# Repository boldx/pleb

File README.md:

# pleb
Phone Line Emulator Board

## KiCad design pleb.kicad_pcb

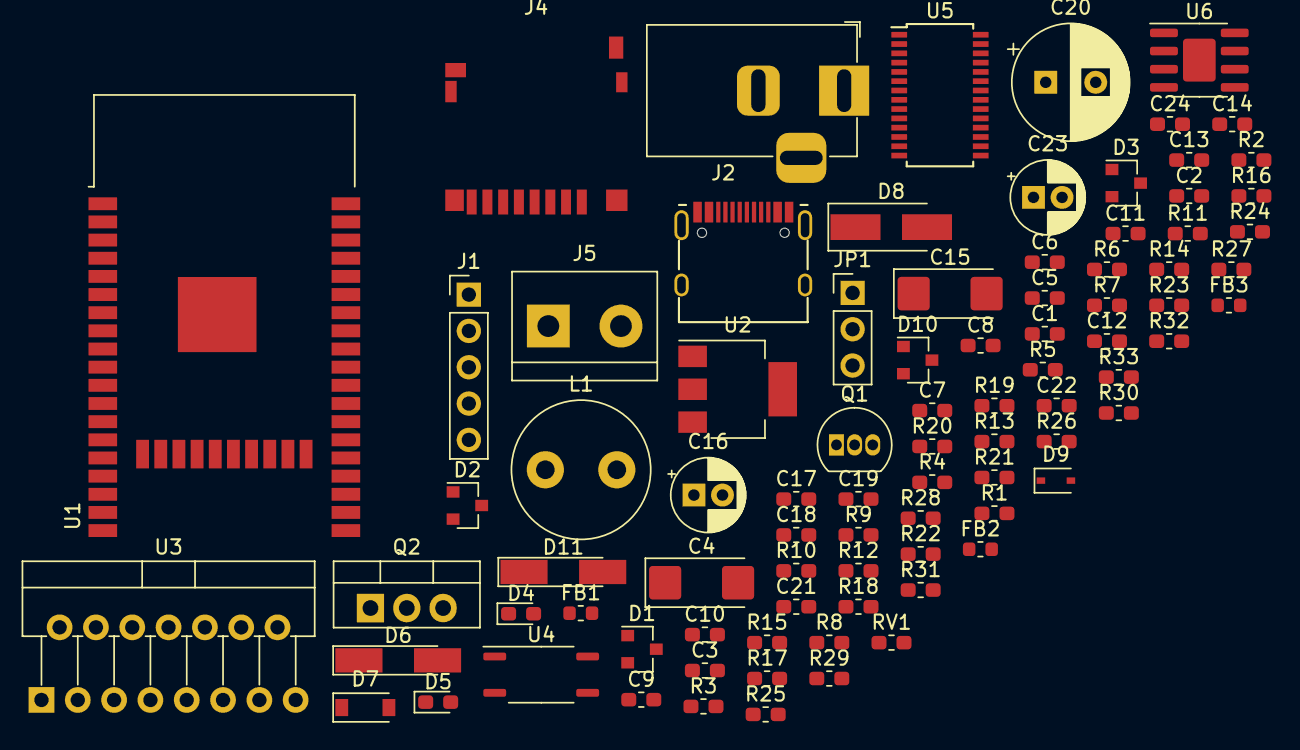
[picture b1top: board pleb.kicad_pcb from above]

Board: 2 copper layers, 87 parts (0 on the bottom side), 59 nets, no tracks yet.

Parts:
C1, C3, C5, C10, C11, C12, C13, C14, C21: 100n; C_0603_1608Metric_Pad1.05x0.95mm_HandSolder
C2, C7, C8, C9, C17, C22: 10u; C_0603_1608Metric_Pad1.05x0.95mm_HandSolder
C4, C15: 10u 25V; CP_EIA-6032-28_Kemet-C_Pad2.25x2.35mm_HandSolder
C6: 100u; C_0603_1608Metric_Pad1.05x0.95mm_HandSolder
C16, C23: 10u 63V; CP_Radial_D5.0mm_P2.00mm
C18: 330n; C_0603_1608Metric_Pad1.05x0.95mm_HandSolder
C19, C24: 100n 63V; C_0603_1608Metric_Pad1.05x0.95mm_HandSolder
C20: 470u; CP_Radial_D8.0mm_P3.50mm
D1, D2, D3: PESD5V0S2BT; SOT-23
D4, D5: LED; LED_0603_1608Metric_Pad1.05x0.95mm_HandSolder
D6, D11: MMBAT46; D_MiniMELF_Handsoldering
D7: BZT52C9V1; D_SOD-123
D8: SS16; D_SMA_Handsoldering
D9: 1N4148WS; D_SOD-323
D10: BZX85C30; D_SOT-23_ANK
FB1, FB2, FB3: Ferrite_Bead; L_0603_1608Metric
J1: Conn_01x05; PinHeader_1x05_P2.54mm_Vertical
J2: Barrel_Jack_Switch; BarrelJack_Horizontal
J3: USB_C_Receptacle_USB2.0; USB-C 16Pin
J4: DM3D-SF
J5: Screw_Terminal_01x02; TerminalBlock_bornier-2_P5.08mm
JP1: Jumper_NC_Dual; PinHeader_1x03_P2.54mm_Vertical
L1: L_Core_Ferrite; L_Radial_D9.5mm_P5.00mm_Fastron_07HVP
Q1: BC546; TO-92_Inline
Q2: IRL530N; TO-220-3_Vertical
R1, R13, R19, R24, R25, R30, R32, R33: 10k; R_0603_1608Metric_Pad1.05x0.95mm_HandSolder
R2, R3, R4, R5, R6, R7, R8, R9, R10, R11: R; R_0603_1608Metric_Pad1.05x0.95mm_HandSolder
R12, R21, R28: 100; R_0603_1608Metric_Pad1.05x0.95mm_HandSolder
R14, R15, R16, R17, R18: 33; R_0603_1608Metric_Pad1.05x0.95mm_HandSolder
R20, R23, R26, R27: 1k; R_0603_1608Metric_Pad1.05x0.95mm_HandSolder
R22, R29, R31: 22k; R_0603_1608Metric_Pad1.05x0.95mm_HandSolder
RV1: 100k; R_0603_1608Metric_Pad1.05x0.95mm_HandSolder
U1: ESP32-WROOM-32; ESP32-WRO-OM-VER
U2: LM1117-3.3; SOT-223-3_TabPin2
U3: L298HN; TO-220-15_P2.54x2.54mm_StaggerOdd_Lead4.58mm_Vertical
U4: TLP185; SOIC-4_4.55x3.7mm_P2.54mm
U5: TLV320AIC23BPW; TSSOP-28_4.4x9.7mm_P0.65mm
U6: LM358; SOIC-8-1EP_3.9x4.9mm_P1.27mm_EP2.29x3mm

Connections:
+3V3: C8.1, D11.1, FB1.1, FB2.2, FB3.2, R10.1, R11.1, R19.2, U2.2
/EN: C1.1, J1.4, R1.2, U1.3
/RXD: J1.2, U1.34
/TXD: J1.3, U1.35
/dcdc_drv: U1.29, U3.5
/dcdc_fb: R22.1, R23.2, U1.4
/dial_det: D11.2, R33.2, U1.36
/hook_det: R19.1, U1.37, U4.6
/i2c_scl: R11.2, U1.12, U5.24
/i2c_sda: R10.2, U1.11, U5.23
/i2s_adc_out: R16.2, U1.7
/i2s_bclk: R15.2, U1.8
/i2s_dac_in: R14.2, U1.10
/i2s_lrclk: R17.2, U1.9
/i2s_mclk: J1.5, R18.2, U1.25
/line_phase_A: U1.30, U3.10
/line_phase_B: U1.31, U3.12
/sd_clk: D1.1, J4.5, R3.2, U1.13
/sd_cmd: D1.2, J4.3, R4.2, U1.23
/sd_d0: D3.2, J4.7, R8.2, U1.24
/sd_d1: D3.1, J4.8, R7.2, U1.26
/sd_d2: D2.2, J4.1, R6.2, U1.14
/sd_d3: D2.1, J4.2, R5.2, U1.16
/sd_det: J4.9, R2.2, U1.6
GND: C1.2, C2.2, C3.2, C4.2, C5.2, C6.2, C7.2, C8.2, C9.2, C10.2, C11.2, C12.2, C13.2, C14.2, C15.2, C16.2, C17.1, C18.1, C19.2, C21.1, C23.2, C24.2, D1.3, D2.3, D3.3, D4.1, D7.2, D9.2, D10.2, J1.1, J2.2, J2.3, J3.A1, J3.B1, J3.S1, J4.6, J4.10, J4.11, Q2.3, R12.2, R23.1, R31.1, U1.1, U1.15, U1.38, U1.39, U2.1, U3.1, U3.8, U4.3, U4.4, U5.11, U5.15, U5.21, U5.22, U5.28, U6.4
unnamed: C2.1, C3.1, FB1.2, J4.4, R2.1, R3.1, R4.1, R5.1, R6.1, R7.1, R8.1
unnamed: C6.1, C7.1, FB2.1, R1.1, U1.2
unnamed: C9.1, C10.1, C12.1, C13.1, C14.1, FB3.1, U5.1, U5.8, U5.14, U5.27
unnamed: C4.1, C5.1, C11.1, C15.1, JP1.2, L1.1, R13.2, U2.3, U3.6, U3.9, U3.11
unnamed: C16.1, C19.1, D8.1, R22.2, R26.2, R27.2, U3.4
unnamed: C17.2, C21.2, RV1.1, U5.16
unnamed: C18.2, C22.2, U5.20
unnamed: C20.1, Q1.1, U3.15
unnamed: C20.2, R21.1, R24.2
unnamed: C22.1, D9.1, R28.2
unnamed: C23.1, C24.1, D10.1, R26.1, R27.1, R30.2, U6.8
unnamed: D4.2, R9.1
unnamed: D5.1, U4.1
unnamed: D5.2, Q1.2, R13.1
unnamed: D6.1, R20.2, U3.2
unnamed: D6.2, D7.1, Q2.1, R20.1
unnamed: D8.2, L1.2, Q2.2
unnamed: J2.1, JP1.3
unnamed: J3.A4, J3.B4, JP1.1
unnamed: J5.1, U3.13
unnamed: J5.2, U3.14
unnamed: Q1.3, R12.1
unnamed: R9.2, U1.33
unnamed: R14.1, U5.4
unnamed: R15.1, U5.3
unnamed: R16.1, U5.6
unnamed: R17.1, U5.5, U5.7
unnamed: R18.1, U5.25
unnamed: R21.2, R25.2, U5.9
unnamed: R24.1, RV1.2, U6.3
unnamed: R25.1, R29.2, U6.2
unnamed: R28.1, R29.1, U6.1, U6.6
unnamed: R30.1, R31.2, R32.1, U6.5
unnamed: R32.2, R33.1, U6.7

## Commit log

2021-08-13 more-or-less finished sch
2021-08-14 move stuff around
2021-08-14 readme
